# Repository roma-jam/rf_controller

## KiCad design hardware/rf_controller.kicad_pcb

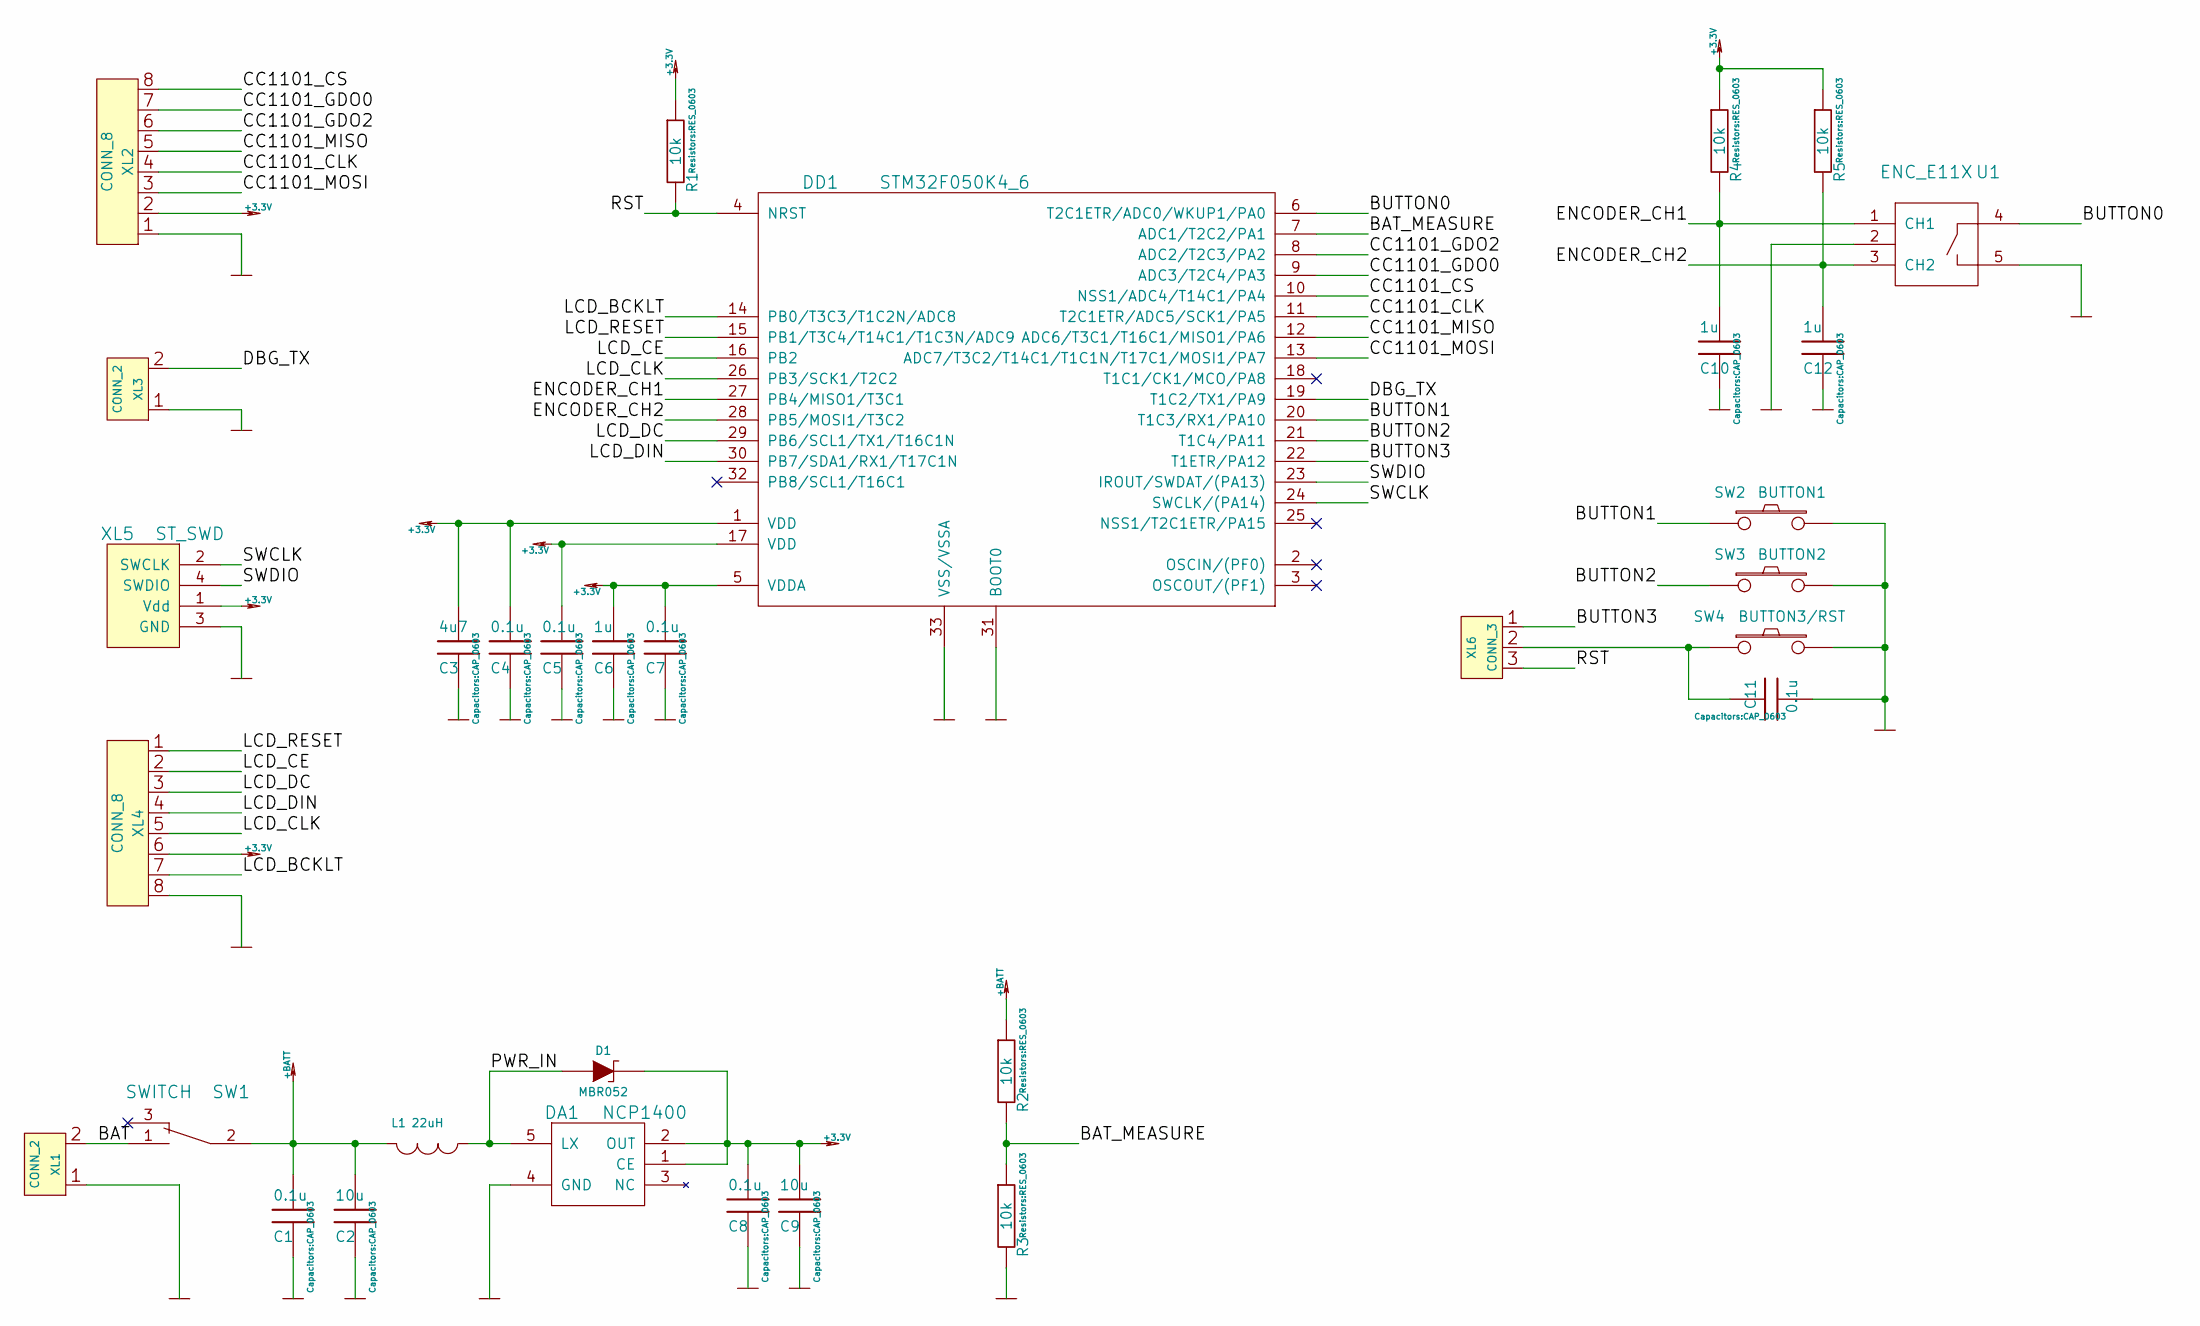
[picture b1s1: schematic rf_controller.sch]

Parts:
C1, C4, C5, C7, C8, C11: 0.1u; CAP_0603
C2, C9: 10u; CAP_0603
C3: 4u7; CAP_0603
C6, C10, C12: 1u; CAP_0603
D1: MBR052; SOD323
DA1: NCP1400; SOT-23-5_HandSoldering
DD1: STM32F050K4_6; QFN-32-1EP_5x5mm_Pitch0.5mm
L1: 22uH; CD_type_6.0X5.5
R1, R2, R3, R4, R5: 10k; RES_0603
SW1: SWITCH; SW_SS-1P2T
SW2: BUTTON1; PUSH_THRHOLE_3-1825910-5
SW3: BUTTON2; PUSH_THRHOLE_3-1825910-5
SW4: BUTTON3/RST; PUSH_THRHOLE_3-1825910-5
U1: ENC_E11X
XL1: CONN_2; 2xBAT_AA_SOLDER
XL2: CONN_8; CC1101_MODULE
XL3: CONN_2; PLS-2
XL4: CONN_8; 84x48_LCD_Module
XL5: ST_SWD; PLS-4
XL6: CONN_3; PLS-3

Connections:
+3.3V: C3.1, C4.1, C5.1, C6.1, C7.1, C8.1, C9.1, D1.C, DA1.1 (CE), DA1.2 (OUT), DD1.1 (VDD), DD1.5 (VDDA), DD1.17 (VDD), R1.1, R4.1, R5.1, XL2.2, XL4.6, XL5.1 (Vdd)
+BATT: C1.1, C2.1, L1.2, R2.1, SW1.2
/BAT: SW1.1, XL1.2 (PM)
/BAT_MEASURE: DD1.7 (ADC1/T2C2/PA1), R2.2, R3.1
/BUTTON0: DD1.6 (T2C1ETR/ADC0/WKUP1/PA0), U1.4
/BUTTON1: DD1.20 (T1C3/RX1/PA10), SW2.1
/BUTTON2: DD1.21 (T1C4/PA11), SW3.1
/BUTTON3: DD1.22 (T1ETR/PA12), XL6.1
/CC1101_CLK: DD1.11 (T2C1ETR/ADC5/SCK1/PA5), XL2.4
/CC1101_CS: DD1.10 (NSS1/ADC4/T14C1/PA4), XL2.8
/CC1101_GDO0: DD1.9 (ADC3/T2C4/PA3), XL2.7
/CC1101_GDO2: DD1.8 (ADC2/T2C3/PA2), XL2.6
/CC1101_MISO: DD1.12 (ADC6/T3C1/T16C1/MISO1/PA6), XL2.5
/CC1101_MOSI: DD1.13 (ADC7/T3C2/T14C1/T1C1N/T17C1/MOSI1/PA7), XL2.3
/DBG_TX: DD1.19 (T1C2/TX1/PA9), XL3.2 (PM)
/ENCODER_CH1: C10.1, DD1.27 (PB4/MISO1/T3C1), R4.2, U1.1 (CH1)
/ENCODER_CH2: C12.1, DD1.28 (PB5/MOSI1/T3C2), R5.2, U1.3 (CH2)
/LCD_BCKLT: DD1.14 (PB0/T3C3/T1C2N/ADC8), XL4.7
/LCD_CE: DD1.16 (PB2), XL4.2
/LCD_CLK: DD1.26 (PB3/SCK1/T2C2), XL4.5
/LCD_DC: DD1.29 (PB6/SCL1/TX1/T16C1N), XL4.3
/LCD_DIN: DD1.30 (PB7/SDA1/RX1/T17C1N), XL4.4
/LCD_RESET: DD1.15 (PB1/T3C4/T14C1/T1C3N/ADC9), XL4.1
/PWR_IN: D1.A, DA1.5 (LX), L1.1
/RST: DD1.4 (NRST), R1.2, XL6.3
/SWCLK: DD1.24 (SWCLK/(PA14)), XL5.2 (SWCLK)
/SWDIO: DD1.23 (IROUT/SWDAT/(PA13)), XL5.4 (SWDIO)
GND: C1.2, C2.2, C3.2, C4.2, C5.2, C6.2, C7.2, C8.2, C9.2, C10.2, C11.1, C12.2, DA1.4 (GND), DD1.31 (BOOT0), DD1.33 (VSS/VSSA), R3.2, SW2.2, SW3.2, SW4.2, U1.2, U1.5, XL1.1, XL2.1, XL3.1, XL4.8, XL5.3 (GND)
unnamed: C11.2, SW4.1, XL6.2 (PM)

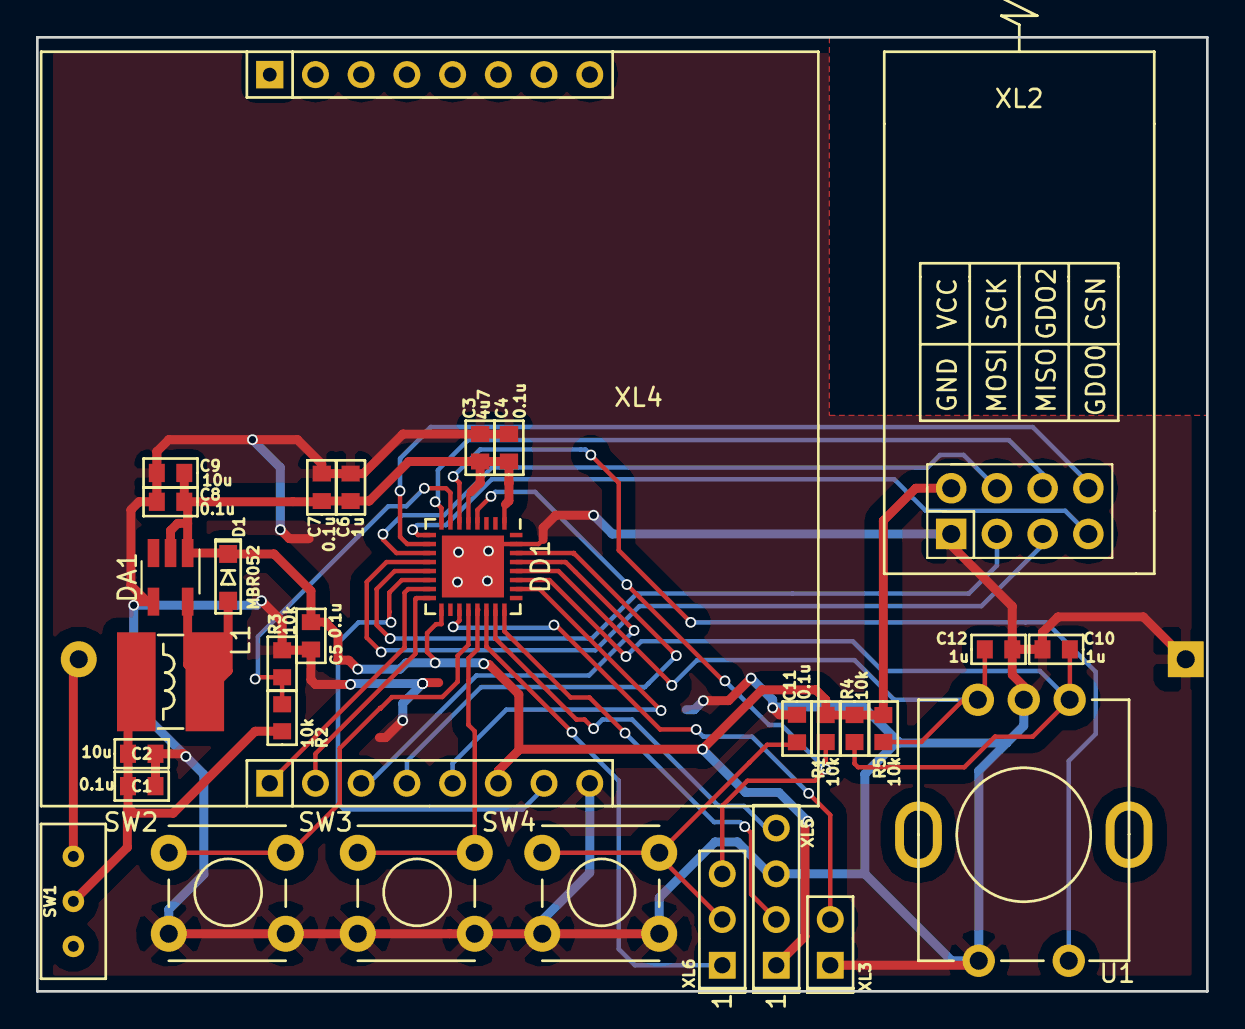
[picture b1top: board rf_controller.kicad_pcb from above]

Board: 2 copper layers, 65.0 x 53.0 mm, 32 parts (1 on the bottom side), 29 nets.

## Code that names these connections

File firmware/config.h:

/*
    RExOS - embedded RTOS
    Copyright (c) 2011-2016, Alexey Kramarenko
    All rights reserved.
*/

#ifndef CONFIG_H
#define CONFIG_H

#define VERSION                                     "0.2b"

#define HOST                                        1
#if !(HOST)
#define CLIENT                                      1
#endif //


#if (HOST)
#if (CLIENT)
#error "HOST and CLIENT could be both"
#endif
#endif
// ============================= BUTTONS ======================================
#define BUTTON_COUNT                                4

#define BUTTON0                                     A0
#define BUTTON1                                     A10
#define BUTTON2                                     A11
#define BUTTON3                                     A12

#define B_PRESS_MS                                  150
#define B_PRESS_LONG_MS                             1000


#define BUTTON_ENCODER_CH1_PIN                      B4
#define BUTTON_ENCODER_CH2_PIN                      B5
#define BUTTON_ENCODER_TIM_REG                      TIM22
#define BUTTON_ENCODER_TIMER                        TIM_22
#define BUTTON_ENCODER_CHANNEL1                     TIM_CHANNEL1
#define BUTTON_ENCODER_CHANNEL2                     TIM_CHANNEL2

#define BUTTON_ENCODER_TIMEOUT_MS                   150


// ============================== BATTERY =====================================
#define BATTERY_ADC                                 ADC1
#define BATTERY_CHANNEL                             STM32_ADC1
#define BATTERY_REFERENCE_MV                        3000
#define BATTERY_ADC_RESOLUTION_BIT                  12
#define BATTERY_MEASURE_PIN                         A1
#define BATTERY_MEASURE_TIMEOUT_MS                  5000
#define BATTERY_INTEGRAL_COUNT                      20

// =============================== LEDS ========================================
#define LED_COUNT                                   4
#define LED_RED_PIN                                 A1
#define LED_BLUE_PIN                                A2
#define LED_ORANGE_PIN                              A15

#define LED_MAX_BRIGHT                              0xFF
#define LED_BLINK_FREQ_HZ                           25
#define LED_BLINK_TIMES                             3

#define LED_TIM_REG                                 TIM2
#define LED_TIM                                     TIM_2
#define LED_RED_CHANNEL                             TIM_CHANNEL2
#define LED_BLUE_CHANNEL                            TIM_CHANNEL3
#define LED_ORANGE_CHANNEL                          TIM_CHANNEL4

#define LED_BLINK_TIM_REG                           TIM3
#define LED_BLINK_TIM                               TIM_3
#define LED_BLINK_TIM_CHANNEL                       TIM_CHANNEL1
#define LED_BLINK_IRQ_VECTOR                        TIM3_IRQn

// ================================ LCD ========================================
#define LCD_DOT_FULL                                0x07
#define LCD_DOT_EMPTY                               0x09
#define LCD_BITBYTE                                 1
#define LCD_SPI                                     0

#define LCD_UPDATE_MS                               200
#define LCD_WIDTH                                   84
#define LCD_HEIGHT                                  48

#define LCD_STR_HEIGHT                              8
#define LCD_STR_WIDTH                               16

/* PINS */
#define LCD_BCKLT_PIN                               B0
#define LCD_RESET_PIN                               B1
#define LCD_CE_PIN                                  B2
#define LCD_SCLK_PIN                                B3
#define LCD_DC_PIN                                  B6
#define LCD_DIN_PIN                                 B7

// =============================== USB =========================================
#define USB_PORT_NUM                                USB_0
#define USBD_PROCESS_SIZE                           1200
#define USBD_PROCESS_PRIORITY                       150

// ============================== CCID  ========================================
#define USB_CCID_INTERFACE                          0
#define USB_HID_INTERFACE                           0

// =============================== COMM ========================================
#define COMM_COMMAND_END                            0x0D

// ================================= DEBUG =====================================

#define DBG_CONSOLE                                 UART_1
#define DBG_CONSOLE_TX_PIN                          A9
#define DBG_CONSOLE_BAUD                            115200

#define TEST_ROUNDS                                 10000

#define APP_DEBUG                                   1
#define APP_DEBUG_ERRORS                            1

#define APP_DEBUG_LCD                               0
#define APP_DEBUG_BUTTON                            1
#define APP_DEBUG_BATTERY                           0

#endif // CONFIG_H

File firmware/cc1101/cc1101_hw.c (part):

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
static inline bool cc1101_busy()
{
    return gpio_get_pin(CC1101_MISO_PIN);
}

static inline bool cc1101_write_register(uint8_t addr, uint8_t data)
{
    gpio_reset_pin(CC1101_CS_PIN);
    while(cc1101_busy());
    spi_byte(CC1101_SPI, addr);
    spi_byte(CC1101_SPI, data);
    gpio_set_pin(CC1101_CS_PIN);
    return true;
}

static inline uint8_t cc1101_read_register(uint8_t addr)
{
    uint8_t res = 0;
    gpio_reset_pin(CC1101_CS_PIN);
    while(cc1101_busy());
    spi_byte(CC1101_SPI, addr | CC_READ_FLAG);
    res = spi_byte(CC1101_SPI, 0);
    gpio_set_pin(CC1101_CS_PIN);
    return res;
}

static inline void cc1101_write_strobe(CC1101_HW* cc1101, uint8_t strobe)
{
    gpio_reset_pin(CC1101_CS_PIN);
    while(cc1101_busy());
    cc1101->status = (uint8_t)spi_byte(CC1101_SPI, strobe);
    gpio_set_pin(CC1101_CS_PIN);
    cc1101->status &= 0b01110000; // Mask needed bits

#if (CC1101_DEBUG_FLOW)
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
    cc1101_flush_tx_fifo(cc1101);

    gpio_reset_pin(CC1101_CS_PIN);
    while(cc1101_busy());

    spi_byte(CC1101_SPI, CC_FIFO | CC_WRITE_FLAG | CC_BURST_FLAG);
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    for(uint8_t i = 0; i < data_size; i++)
        spi_byte(CC1101_SPI, data[i]);

    gpio_set_pin(CC1101_CS_PIN);
}

static inline void cc1101_chip_reset(CC1101_HW* cc1101)
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static inline void cc1101_gdo0_irq(int vector, void* param)
{
    CC1101_HW* cc1101 = (CC1101_HW*)param;
    EXTI->PR = 1ul << GPIO_PIN(CC1101_GDO0_PIN);
    NVIC_DisableIRQ(CC1101_GDO0_EXTI_IRQ);

#if (CC1101_DEBUG_FLOW)
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
    cc1101->state = CC1101_STATE_OFF;

    pin_enable(CC1101_CLK_PIN, STM32_GPIO_MODE_AF | GPIO_SPEED_HIGH, AF0);
    pin_enable(CC1101_MISO_PIN, STM32_GPIO_MODE_AF | GPIO_SPEED_HIGH, AF0);
    pin_enable(CC1101_MOSI_PIN, STM32_GPIO_MODE_AF | GPIO_SPEED_HIGH, AF0);
    gpio_enable_pin(CC1101_CS_PIN, GPIO_MODE_OUT);

    gpio_enable_pin(CC1101_GDO0_PIN, GPIO_MODE_IN_FLOAT);
//    gpio_enable_pin(CC1101_GDO2_PIN, GPIO_MODE_IN_FLOAT);


    pin_enable_exti(CC1101_GDO0_PIN, EXTI_FLAGS_FALLING);
    irq_register(CC1101_GDO0_EXTI_IRQ, cc1101_gdo0_irq, (void*)cc1101);
    NVIC_SetPriority(CC1101_GDO0_EXTI_IRQ, 7);

    gpio_set_pin(CC1101_CS_PIN);

    if(!spi_open(CC1101_SPI, SPI_MODE_MASTER |
                                 SPI_DATA_BO_MSB |
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#endif // CC1101_DEBUG_REQUESTS
    cc1101->state = CC1101_STATE_OFF;
    spi_close(CC1101_SPI);
    pin_disable(CC1101_CS_PIN);
    pin_disable(CC1101_CLK_PIN);
    pin_disable(CC1101_MISO_PIN);
    pin_disable(CC1101_MOSI_PIN);
    pin_disable(CC1101_GDO0_PIN);
    pin_disable(CC1101_GDO2_PIN);
}

void cc1101_hw_reset(CC1101_HW* cc1101)
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
    if(status & CC_STATUS_CRC_OK)
    {
        gpio_reset_pin(CC1101_CS_PIN);
        while(cc1101_busy());

        spi_byte(CC1101_SPI, CC_FIFO | CC_READ_FLAG | CC_BURST_FLAG);
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        // dummy LQI
        data[res++] = spi_byte(CC1101_SPI, 0);

        gpio_set_pin(CC1101_CS_PIN);

        io->data_size = res;
#if (CC1101_DEBUG_FLOW)
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
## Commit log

2018-10-19 + Add hardware project
2018-10-19 + Add pcb
2018-11-14 + Add FW project; + Add HW gerber files.
2018-11-14 + Add main button press events.
2018-11-18 Trying to launch CC1101...
2018-11-19 + Decrease CC1101 SPI clocking + Add ADC + Add buttons 1,2,3
2018-11-19 + Add HOST and CLIENT button test
2018-11-19 + Encoder settings
2018-11-20 Trying to launch radio channel ...
2018-11-20 + Add another CC1101 configuse, but still not working ...
2018-11-21 + CC1101 finally works.
2018-11-21 + Some strange data corruption on TX side. Perhaps, cause CRC is ok, packet received correctly but packet data is not valid.
2018-11-21 Read packet length register doesn't not correct. Seems to SPI doesn't work well.
2018-11-21 + Increase pin speed. Now packet received correctly.
2018-11-21 + Switch off some debug information on CC1101 level.
2018-11-24 + Make a test power setup on CC1101 by encoder
2019-03-07 + Add timeout to cc1101 receive function.
2019-03-07 + Add button selection between channel and power.
